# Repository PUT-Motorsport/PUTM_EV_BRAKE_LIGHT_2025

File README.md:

# **PUTM_EV_Brake_Light**

Old project brake light, modified, used in PM09.

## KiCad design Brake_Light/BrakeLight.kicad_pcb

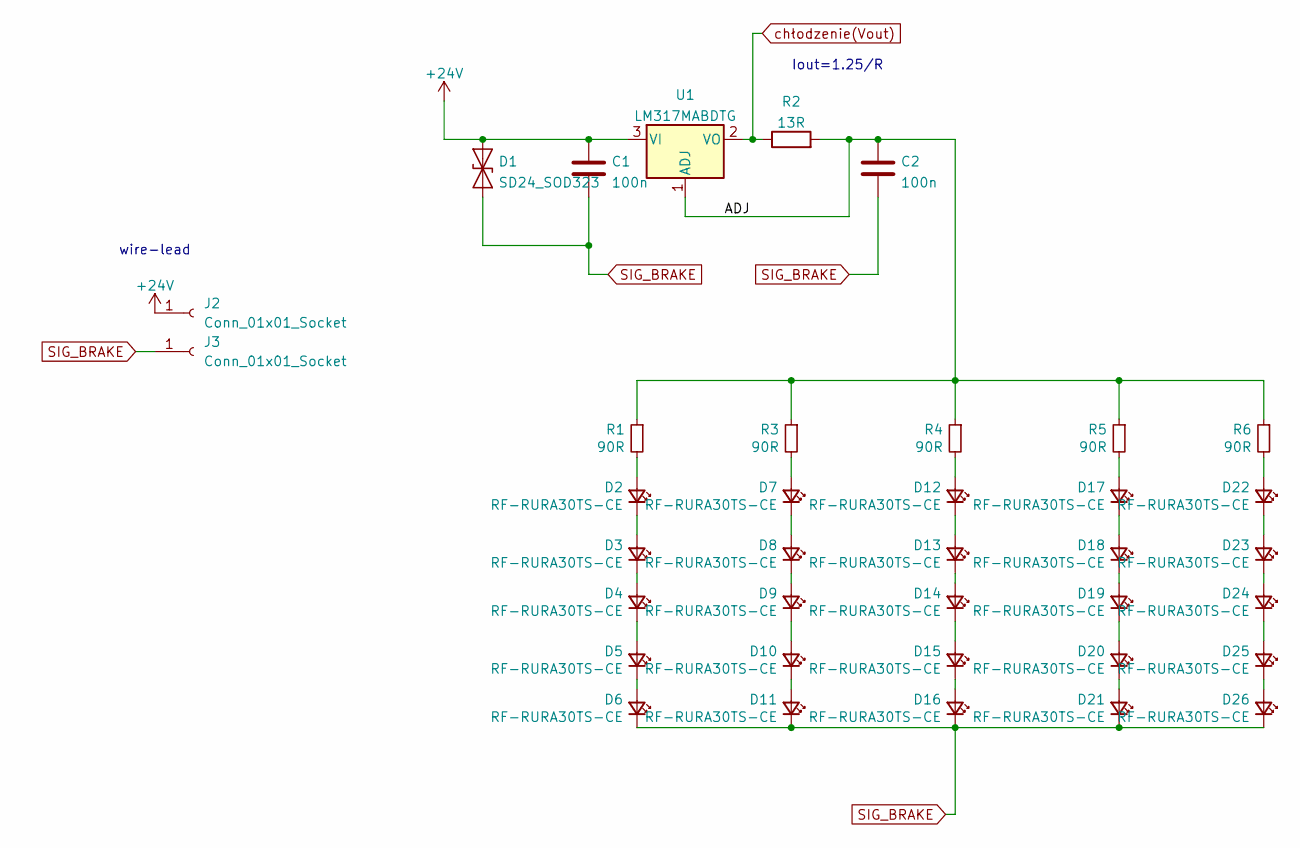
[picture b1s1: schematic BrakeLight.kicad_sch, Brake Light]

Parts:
C1, C2: 100n; C_0603_1608Metric
D1: SD24_SOD323; D_SOD-323
D2, D3, D4, D5, D6, D7, D8, D9, D10, D11, D12, D13, D14, D15, D16, D17, D18, D19, D20, D21, D22, D23, D24, D25, D26: RF-RURA30TS-CE; LED_PLCC-2
J2, J3: Conn_01x01_Socket; SolderWire-0.75sqmm_1x01_D1.25mm_OD3.5mm
R1, R3, R4, R5, R6: 90R; R_1206_3216Metric
R2: 13R; R_1206_3216Metric
U1: LM317MABDTG; NVD5117PLT4GVF01

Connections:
+24V: C1.1, D1.1 (A1), J2.1, U1.3 (VI)
/ADJ: C2.1, R1.1, R2.2, R3.1, R4.1, R5.1, R6.1, U1.1 (ADJ)
unnamed: D2.2 (A), R1.2
unnamed: D2.1 (K), D3.2 (A)
unnamed: D3.1 (K), D4.2 (A)
unnamed: D4.1 (K), D5.2 (A)
unnamed: D5.1 (K), D6.2 (A)
unnamed: D7.2 (A), R3.2
unnamed: D7.1 (K), D8.2 (A)
unnamed: D8.1 (K), D9.2 (A)
unnamed: D9.1 (K), D10.2 (A)
unnamed: D10.1 (K), D11.2 (A)
unnamed: D12.2 (A), R4.2
unnamed: D12.1 (K), D13.2 (A)
unnamed: D13.1 (K), D14.2 (A)
unnamed: D14.1 (K), D15.2 (A)
unnamed: D15.1 (K), D16.2 (A)
unnamed: D17.2 (A), R5.2
unnamed: D17.1 (K), D18.2 (A)
unnamed: D18.1 (K), D19.2 (A)
unnamed: D19.1 (K), D20.2 (A)
unnamed: D20.1 (K), D21.2 (A)
unnamed: D22.2 (A), R6.2
unnamed: D22.1 (K), D23.2 (A)
unnamed: D23.1 (K), D24.2 (A)
unnamed: D24.1 (K), D25.2 (A)
unnamed: D25.1 (K), D26.2 (A)
SIG_BRAKE: C1.2, C2.2, D1.2 (A2), D6.1 (K), D11.1 (K), D16.1 (K), D21.1 (K), D26.1 (K), J3.1
chłodzenie(Vout): R2.1, U1.2 (VO)

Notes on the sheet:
wire-lead
Iout=1.25/R

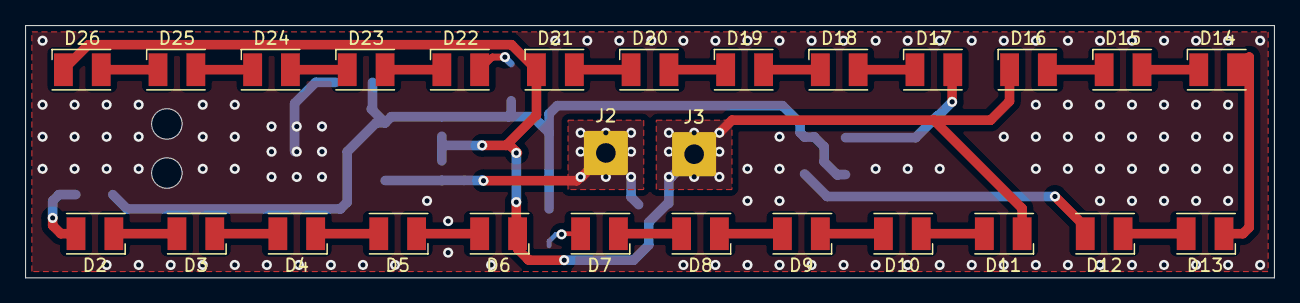
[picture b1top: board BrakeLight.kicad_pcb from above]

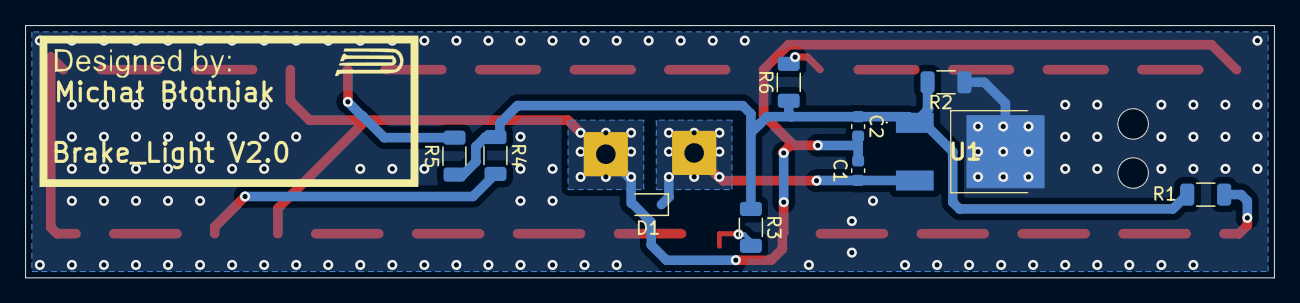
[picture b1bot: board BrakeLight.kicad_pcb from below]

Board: 2 copper layers, 99.0 x 20.0 mm, 37 parts (10 on the bottom side), 29 nets.

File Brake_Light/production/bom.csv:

Designator,Footprint,Quantity,Value,LCSC Part #
"C1, C2",0603,2,100n,
D1,D_SOD-323,1,SD24_SOD323,
"D10, D11, D12, D13, D14, D15, D16, D17, D18, D19, D2, D20, D21, D22, D23, D24, D25, D26, D3, D4, D5, D6, D7, D8, D9",LED_PLCC-2,25,RF-RURA30TS-CE,
"J2, J3",SolderWire-0.75sqmm_1x01_D1.25mm_OD3.5mm,2,Conn_01x01_Socket,
"R1, R3, R4, R5, R6",1206,5,90R,
R2,1206,1,13R,
U1,NVD5117PLT4GVF01,1,LM317MABDTG,

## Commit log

2024-06-07 Brakelight hardware
2024-06-14 Adapted to PM09
    Changing the power footprint and changing several tracks
2024-06-14 Add unsave changes
2024-06-19 Changing the housing of the LED section resistors to larger ones 0603 -> 1206
2024-06-25 Changing the sizes of holes for attaching cables
2025-01-22 Upgrade old version
2025-01-22 Change name folder
2025-01-27 Visual changes and preparation for execution
2025-01-27 Add gitignore file
2025-01-27 Cleaning
2025-01-28 Upgrade zones and via
